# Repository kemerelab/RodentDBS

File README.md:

Rodent Stimulation Module Project
=========

Rodent-scale open source programmable constant current deep brain stimulation system. Runs on a
low power MSP430 microcontroller from Texas Instrumnents. Interfaces with an Android app using
Near Field Communication (NFC).

   - The [Firmware/](Firmware/) directory contains the code which runs on the MSP430. 
   - The [AppCode/](AppCode/) directory contains the Android Studio project and code for the
     NFC controller app.
   - The [PCBs/](PCBs/) directory contains the design files for the printed circuit board
     hardware.

#### Physical Size of Devices In Action

The most recent version of the hardware is about 1/4" thick including a CR2032 battery, and a
little larger than a quarter in footprint. Battery life is about 200 hours. In photos above,
major grid is 1/2".

#### Biphasic Constant Current Stimulation

Current measurements (voltage over the series 10 K resistor)
for a 90 µA, 60 µs, 120 Hz stimulation settings.

Developed by members of the [Kemere Lab](http://rnel.rice.edu) at Rice University. This work
was supported by the National Science Foundation (NSF CAREER Award CBET-1351692) and Texas
Instruments, Inc. Any opinions, findings, and conclusions or recommendations expressed in this
material are those of the author(s) and do not necessarily reflect the views of the National
Science Foundation.

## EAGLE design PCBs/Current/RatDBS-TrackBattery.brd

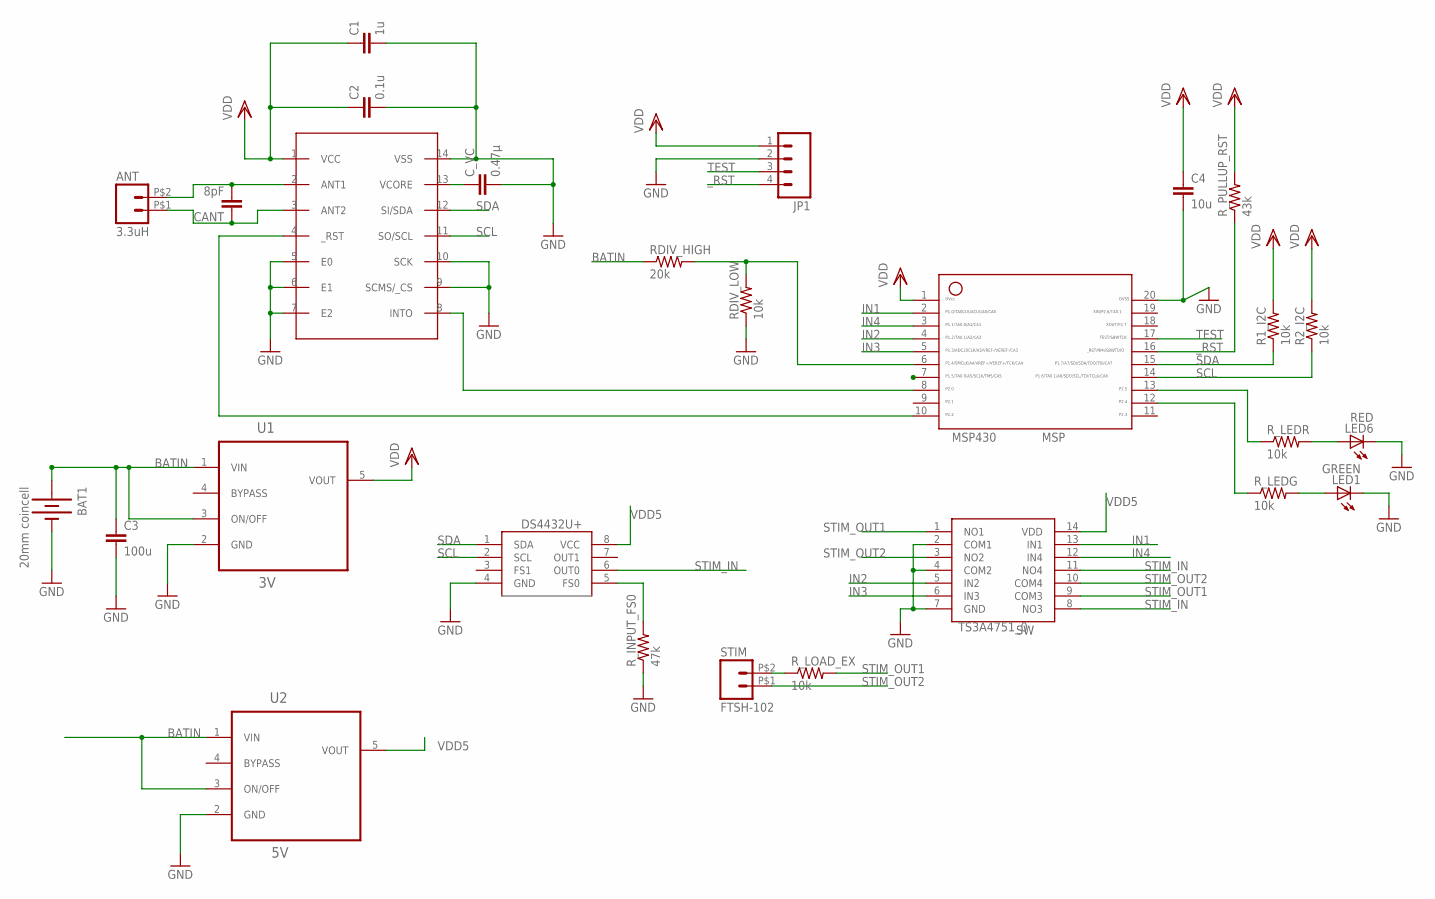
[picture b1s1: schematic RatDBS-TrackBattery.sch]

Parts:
ANT: 3.3uH; FTSH-102-DH
BAT1: 20mm coincell; BATTCOM_20MM_PLASTIC_STUDS
C1: 1u; C0603
C2: 0.1u; C0603
C3: 100u; C1206
C4: 10u; C1206
CANT: 8pF; C0603
C_VC: 0.47µ; C0603
DS4432U+: DS4432U+; 8_PIN
JP1: M041.27MM; 1X04-1.27MM
LED1: GREEN; LED-1206
LED6: RED; LED-1206
MSP430: MSP; 20_PIN
R1_I2C, R2_I2C: 10k; R0603
RDIV_HIGH: 20k; R0603
RDIV_LOW: 10k; R0603
R_INPUT_FS0: 47k; R0603
R_LEDG: 10k; R0603
R_LEDR: 10k; R0603
R_LOAD_EX: 10k; R0603
R_PULLUP_RST: 43k; R0603
STIM: FTSH-102; FTSH-102-DH
TS3A4751_0: SW; 14_PIN
U1: 3V; SOT95P280X145-5N
U2: 5V; SOT95P280X145-5N
U$1: NFC; PW_R-PDSO-G14

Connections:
BATIN: BAT1.1 (+), C3.1, RDIV_HIGH.1, U1.1 (VIN), U1.3 (ON/OFF), U2.1 (VIN), U2.3 (ON/OFF)
GND: BAT1.2 (-), C1.2, C2.2, C3.2, C4.2, C_VC.2, DS4432U+.4 (GND), JP1.2, LED1.C, LED6.C, MSP430.20, RDIV_LOW.1, R_INPUT_FS0.1, TS3A4751_0.2 (COM1), TS3A4751_0.4 (COM2), TS3A4751_0.7 (GND), U1.2 (GND), U2.2 (GND), U$1.5 (E0), U$1.6 (E1), U$1.7 (E2), U$1.9 (SCMS/_CS), U$1.10 (SCK), U$1.14 (VSS)
IN1: MSP430.2, TS3A4751_0.13 (IN1)
IN2: MSP430.4, TS3A4751_0.5 (IN2)
IN3: MSP430.5, TS3A4751_0.6 (IN3)
IN4: MSP430.3, TS3A4751_0.12 (IN4)
unnamed: C_VC.1, U$1.13 (VCORE)
unnamed: ANT.P$2 (2), CANT.2, U$1.2 (ANT1)
unnamed: MSP430.8, U$1.8 (INTO)
unnamed: R_LOAD_EX.1, STIM.P$2 (2)
unnamed: MSP430.13, R_LEDR.1
unnamed: MSP430.10, U$1.4 (_RST)
unnamed: DS4432U+.5 (FS0), R_INPUT_FS0.2
unnamed: LED6.A, R_LEDR.2
unnamed: MSP430.6, RDIV_HIGH.2, RDIV_LOW.2
unnamed: MSP430.12, R_LEDG.1
unnamed: ANT.P$1 (1), CANT.1, U$1.3 (ANT2)
unnamed: LED1.A, R_LEDG.2
SCL: DS4432U+.2 (SCL), MSP430.14, R2_I2C.1, U$1.11 (SO/SCL)
SDA: DS4432U+.1 (SDA), MSP430.15, R1_I2C.1, U$1.12 (SI/SDA)
STIM_IN: DS4432U+.6 (OUT0), TS3A4751_0.8 (NO3), TS3A4751_0.11 (NO4)
STIM_OUT1: R_LOAD_EX.2, TS3A4751_0.1 (NO1), TS3A4751_0.9 (COM3)
STIM_OUT2: STIM.P$1 (1), TS3A4751_0.3 (NO2), TS3A4751_0.10 (COM4)
TEST: JP1.3, MSP430.17
VDD: C1.1, C2.1, C4.1, JP1.1, MSP430.1, R1_I2C.2, R2_I2C.2, R_PULLUP_RST.2, U1.5 (VOUT), U$1.1 (VCC)
VDD5: DS4432U+.8 (VCC), TS3A4751_0.14 (VDD), U2.5 (VOUT)
_RST: JP1.4, MSP430.16, R_PULLUP_RST.1

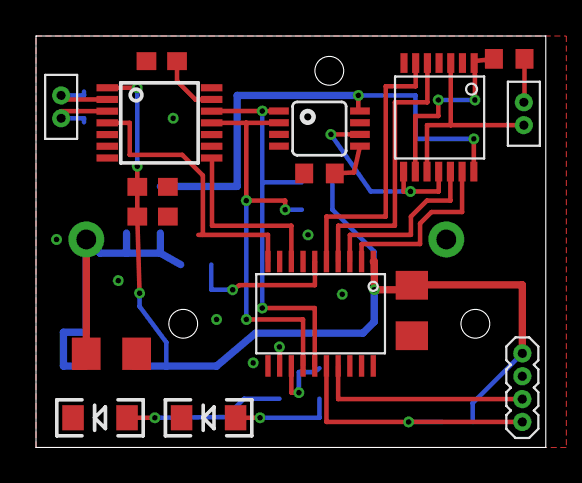
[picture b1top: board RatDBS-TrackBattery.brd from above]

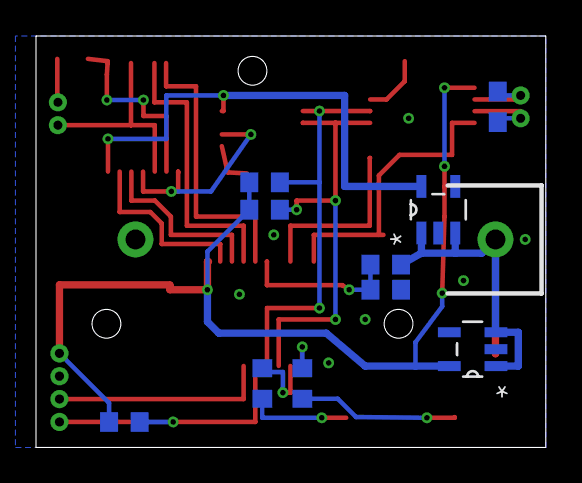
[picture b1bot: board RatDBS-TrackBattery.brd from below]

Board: 2 copper layers, 28.3 x 22.9 mm, 27 parts (11 on the bottom side), 27 nets.

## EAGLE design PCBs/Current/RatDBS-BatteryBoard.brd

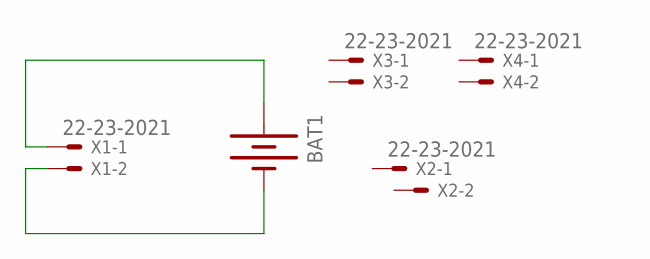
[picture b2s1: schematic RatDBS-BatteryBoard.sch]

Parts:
BAT1: BATTERY; BATTCOM_20MM_PLASTIC_STUDS
X1, X2, X3, X4: 22-23-2021

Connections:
BATIN: BAT1.1 (+), X1.1
GND: BAT1.2 (-), X1.2

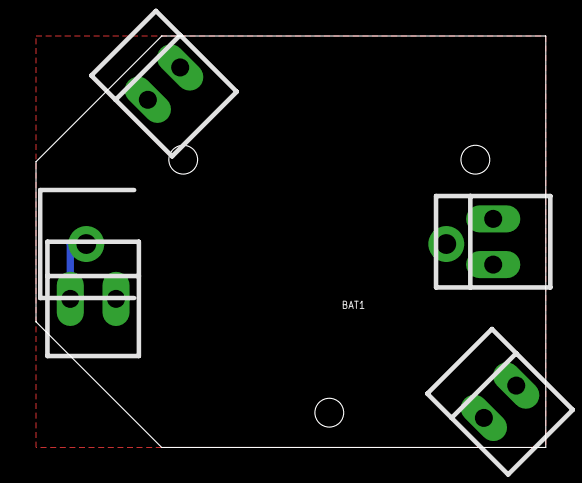
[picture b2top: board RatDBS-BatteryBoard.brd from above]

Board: 2 copper layers, 28.3 x 22.9 mm, 5 parts (0 on the bottom side), 2 nets.

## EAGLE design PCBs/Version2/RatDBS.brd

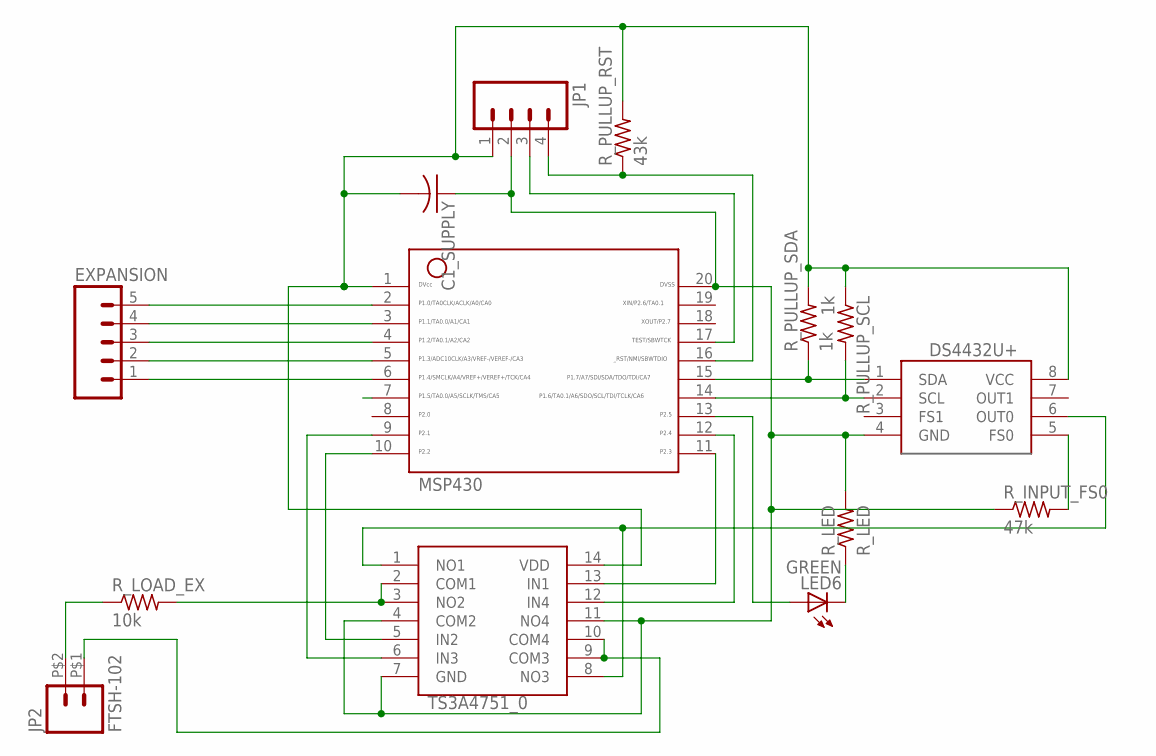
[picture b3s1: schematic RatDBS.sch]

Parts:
C1_SUPPLY: C-USC0603; C0603
DS4432U+: DS4432U+; 8_PIN
EXPANSION: M051.27MM; 1X05-1.27MM
JP1: M041.27MM; 1X04-1.27MM
JP2: FTSH-102; FTSH-102-DH
LED6: GREEN; LED-1206
MSP430: MSP430; 20_PIN
R_INPUT_FS0: 47k; R0603
R_LED: R_LED; R0603
R_LOAD_EX: 10k; R0603
R_PULLUP_RST: 43k; R0603
R_PULLUP_SCL: 1k; R0603
R_PULLUP_SDA: 1k; R0603
TS3A4751_0: TS3A4751; 14_PIN

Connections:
CURRENT0: DS4432U+.6 (OUT0), TS3A4751_0.1 (NO1), TS3A4751_0.8 (NO3)
GND: C1_SUPPLY.1, DS4432U+.4 (GND), JP1.2, MSP430.20, R_INPUT_FS0.1, R_LED.2, TS3A4751_0.4 (COM2), TS3A4751_0.7 (GND), TS3A4751_0.11 (NO4)
IN1: MSP430.11, TS3A4751_0.13 (IN1)
IN2_0: MSP430.10, TS3A4751_0.5 (IN2)
IN3_0: MSP430.9, TS3A4751_0.6 (IN3)
IN4: MSP430.12, TS3A4751_0.12 (IN4)
LOAD1_0: R_LOAD_EX.2, TS3A4751_0.2 (COM1), TS3A4751_0.3 (NO2)
LOAD2_0: JP2.P$1 (1), TS3A4751_0.9 (COM3), TS3A4751_0.10 (COM4)
unnamed: DS4432U+.2 (SCL), MSP430.14, R_PULLUP_SCL.2
unnamed: DS4432U+.1 (SDA), MSP430.15, R_PULLUP_SDA.1
unnamed: EXPANSION.1, MSP430.6
unnamed: JP2.P$2 (2), R_LOAD_EX.1
unnamed: LED6.A, MSP430.13
unnamed: EXPANSION.2, MSP430.5
unnamed: DS4432U+.5 (FS0), R_INPUT_FS0.2
unnamed: LED6.C, R_LED.1
unnamed: EXPANSION.3, MSP430.4
unnamed: EXPANSION.4, MSP430.3
unnamed: EXPANSION.5, MSP430.2
TEST: JP1.3, MSP430.17
VDD: C1_SUPPLY.2, DS4432U+.8 (VCC), JP1.1, MSP430.1, R_PULLUP_RST.2, R_PULLUP_SCL.1, R_PULLUP_SDA.2, TS3A4751_0.14 (VDD)
_RST: JP1.4, MSP430.16, R_PULLUP_RST.1

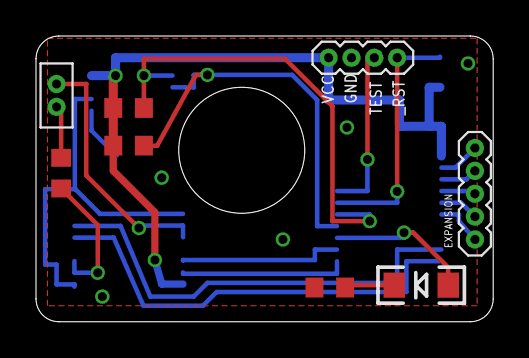
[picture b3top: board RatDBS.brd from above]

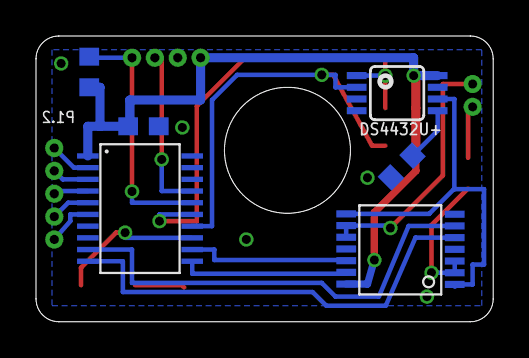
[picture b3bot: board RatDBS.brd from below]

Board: 2 copper layers, 25.4 x 15.9 mm, 14 parts (6 on the bottom side), 22 nets.

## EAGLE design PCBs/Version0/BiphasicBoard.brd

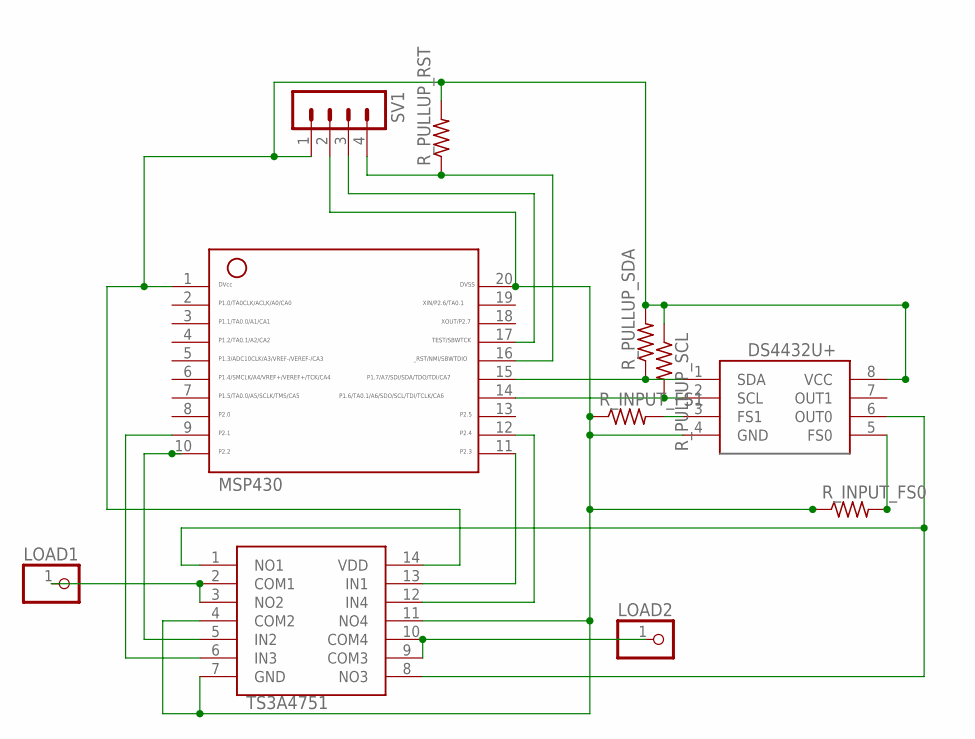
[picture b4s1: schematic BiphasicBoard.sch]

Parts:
DS4432U+: DS4432U+; 8_PIN
LOAD1, LOAD2: PINHD-1X1; 1X01
MSP430: MSP430; 20_PIN
R_INPUT_FS0, R_INPUT_FS1: R-US_R0603; R0603
R_PULLUP_RST: R-US_R0603; R0603
R_PULLUP_SCL: R-US_R0603; R0603
R_PULLUP_SDA: R-US_R0603; R0603
SV1: MA04-1
TS3A4751: TS3A4751; 14_PIN

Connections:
CURRENT0: DS4432U+.6 (OUT0), TS3A4751.1 (NO1), TS3A4751.8 (NO3)
GND: DS4432U+.4 (GND), MSP430.20, R_INPUT_FS0.1, R_INPUT_FS1.1, SV1.2, TS3A4751.4 (COM2), TS3A4751.7 (GND), TS3A4751.11 (NO4)
IN1: MSP430.11, TS3A4751.13 (IN1)
IN4: MSP430.12, TS3A4751.12 (IN4)
LOAD1: LOAD1.1, TS3A4751.2 (COM1), TS3A4751.3 (NO2)
LOAD2: LOAD2.1, TS3A4751.9 (COM3), TS3A4751.10 (COM4)
unnamed: DS4432U+.2 (SCL), MSP430.14, R_PULLUP_SCL.2
unnamed: DS4432U+.1 (SDA), MSP430.15, R_PULLUP_SDA.1
unnamed: MSP430.10, TS3A4751.5 (IN2)
unnamed: DS4432U+.5 (FS0), R_INPUT_FS0.2
unnamed: MSP430.9, TS3A4751.6 (IN3)
TEST: MSP430.17, SV1.3
VDD: DS4432U+.8 (VCC), MSP430.1, R_PULLUP_RST.2, R_PULLUP_SCL.1, R_PULLUP_SDA.2, SV1.1, TS3A4751.14 (VDD)
VIA1: DS4432U+.3 (FS1), R_INPUT_FS1.2
_RST: MSP430.16, R_PULLUP_RST.1, SV1.4

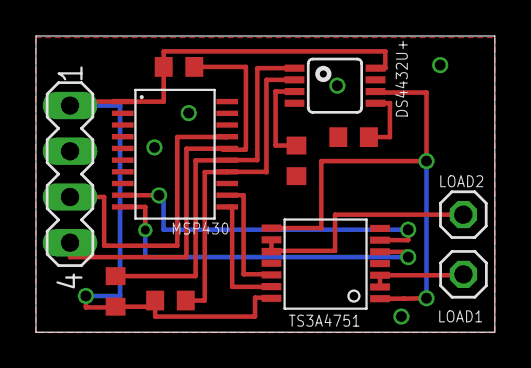
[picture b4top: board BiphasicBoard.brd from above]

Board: 2 copper layers, 25.5 x 16.5 mm, 11 parts (0 on the bottom side), 15 nets.

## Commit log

2014-05-19 Initial RatDBS commit
2014-05-19 Added gitignore
2014-05-19 Added license
2014-05-19 Changed directory structure
2014-05-19 Added manufacturing files
2014-05-19 Editted design
2014-05-20 Updated Library Parts
2014-05-20 Fixed DRU file
2014-05-20 Updated Board
    Updated the board design to comply with the DRC of Seed_DRU
2014-06-20 Version 1.0 Changes 1) Dual channel biphasic current output; 2) LED to indicate power supply status.
2014-06-20 Version 1.1 Changes 1) Added a voltage divider to measure power supply level 2) Removed impedence measurement in one of the biphasic current output channels
2014-06-20 Made a few cosmetic changes
2014-06-20 Smashed a bunch of parts. Changed font sizes to 25 mil, 15% ratio
2014-06-20 Added values layers to cam silkscreen
2014-06-20 Fixed error just introduced in CAM job. Further added values. Labels for power.
2014-06-20 Changed gitignore and added manufacturing zip files
2014-07-04 1) Corrected resistor name&values; 2) Added resistor for LED.
2014-07-06 Smashed LED resistor, changed font to 25/16%/Vector, rounded corners.
2014-07-09 Moved some wires around to make ground plane larger.
2014-07-17 MSP code to use with version 1 pcb.
2014-07-17 Code to use with version 1 pcb
2014-07-20 7/20/2014 B.M. Fixed code and comments.
2014-07-21 Added Matlab codes for calculating DS4432 settings. --B.M.
2014-11-06 Updated randomized version of the DBS board (c code, not tested). 11/06/2014
2015-05-08 Added single channel stimulator
2015-06-20 IPG+Bluetooth Module
    Code for IPG with bluetooth module
2015-07-08 Changed colors and put values onto PCB
2015-08-16 Changed some colors and labels, changed code directory structure, and added docs for RF430
2015-08-26 Moved gitignore into PCBs directory and repaired Seeed CAM file for EAGLE 7
2015-08-26 Added NFC-controlled PCB and I2C command list
2015-08-26 Renamed Code to Firmware in preparation for moving Android Project
2015-08-26 Added Android app project
2015-08-26 Fixed layout so that it doesn't overflow
2015-09-02 Add CCS project files.
2015-09-02 fixed gitignore for ccs and added files
2015-09-05 Added code for NFC PCB firmware. Compiles (but untested). No NFC hooks yet.
2015-09-05 Found bug in PCB - switch matrix not wired up correctly. Fixed, and added interrupt and reset connections to MSP430
2015-09-05 Added NFC hello world message. Still not functionality tested.
2015-09-07 Fixed I2C communication so that "hello world" is now being pushed to NFC device. Was a royal pain. Had to give up on polling I2C because stop condition was generated too early so last byte always got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
2015-09-08 Reformatted I2C code and updated ISR declarations
2015-09-09 Changed NDEF to packed struct format
2015-09-09 speed up time 10x
2015-09-10 Switched to external NDEF record type to allow for binary data. Changed app and firmware. Working.
2015-09-11 Reformatted globals so that DeviceData is now a global structure that corresponds to NDEF message
2015-09-11 Deleted excess NDEF TextRecord info
2015-09-11 Further deletions of code to convert numbers to strings
2015-09-11 More deletions. Also fixed memory leak bug in I2C string.
2015-09-11 Wowser. Finally figured out I2C receive, transmit, and transmit/receive.
2015-09-11 Reformatted lastUpdate in android app
2015-09-11 Added ability to enable/disable stimulation
2015-09-15 Reasonable battery life. Still haven't tested switches or current source yet.
2015-09-17 Improved android app, also changed communication format
2015-09-17 Adding files
2015-09-18 Working; added firmware version checking
2015-09-18 Created board test CCS/Energia project. More changes in android app
2015-09-18 Added CCS files for BoardTest.
2015-09-18 Cleaned up android project by removing unnecessary dependencies
2015-09-19 Added some hacks that appear to fix transitions from programming RF430 to DS4432
2015-09-21 Seemingly working
2015-09-23 Two more boards with integrated CR2032 battery holders. More doc pds, improved code.
2015-09-23 Changed PowerBudget to README
2015-09-23 Moved docs to Firmware subdirectory and added a bit more Readme content
2015-09-23 Fixed board errors that were fixed in panelized version
2015-09-24 Made I2C 333 kHz instead of 100
2015-09-25 Cleaned up file/directory structure for PCBs
2015-09-25 Rearranged directory structure and added Board.h with constants which depend on board revision
2015-09-26 Updated README about power consumption
    removed some
2015-09-28 Added jitter to firmware (now version 5) and updated android app. also fixed some bugs, such as up/back issue
2015-09-30 Moved some things around and added another README
2015-09-30 Resized screenshots in README
2015-09-30 Resized screenshots in README again
2015-09-30 Updated main README
2015-09-30 Fixed links in main README
2015-09-30 Updated README in Firmware directory
2015-09-30 Fixed links in Firmware README
2015-09-30 Updated main README with a picture
2015-10-02 Reordered some code and fixed bug so that edit toggle is disabled by default.
2015-10-05 Switched all settings to dropdown menus
2015-10-05 Removed excess dialog stuff after switching to spinners. Fixed onsave/onrestore to properly deal with enable switch toggle.
2015-10-05 Updated to version 2 (0.1).
2015-10-05 Fixed bug where jitter was not accurate. Now subtrace half of jitter max before adding random value
2015-10-05 Fixed bug in the size of the buffer used for firmware version 5
2015-10-09 Switched I2C back to 100 kHz and fixed bug where unsigned int timer counters could underflow
2015-10-12 Added an error state until NFC is read correctly.
2015-10-16 Changed micro to milli in jitter value dropdown menu
2015-10-16 Changes made in order to get stimulation working with new modules. (1) Had to properly assign pins for switch matrix. (2) Had to boost master clock to 8 MHz so that stim interrupt would actually be a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
2015-10-16 Updated main README file
2015-10-16 Changed BMPs for PNGs
2015-10-16 Fixed README
2015-10-16 Editted README
2016-06-03 Update README.md
    Added supproters.
2016-06-03 Added supporter pngs for website and updated PCBs.
2017-02-27 Updated PCB manufacturing
2017-05-24 Updated README for NSF reporting
2017-07-03 Updated primary design and added two component (battery-on-separate-pcb) version)
2017-09-14 Adds low battery notification LED. Implements jitter. Updates voltage calculation for dual cell stimulator.
2017-10-17 App Screenshots for README
2017-10-18 Added google play APK to repository
    Google play downloads outside of the US are limited. This APK file can be manually added to android devices and installed through the file manager. Tested with OI File Manager.
2017-10-23 Added resistor values for voltage divider and LEDs. Labeled preferred 332 inductor antenna and CANT values.
2018-10-13 Added solidparts and STLs for headcap assembly. Contains readme and render for construction.
2019-01-08 Added estimated power notebook

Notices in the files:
PCBs/Current/RatDBS-BatteryBoard.brd:
(C) 2017
PCBs/Current/RatDBS-TrackBattery.brd:
v3.0 (C)2017
parts and their libraries:
SparkFun-LED: Licensing: CC v3.0 Share-Alike You are welcome to use this library for commercial purposes.
